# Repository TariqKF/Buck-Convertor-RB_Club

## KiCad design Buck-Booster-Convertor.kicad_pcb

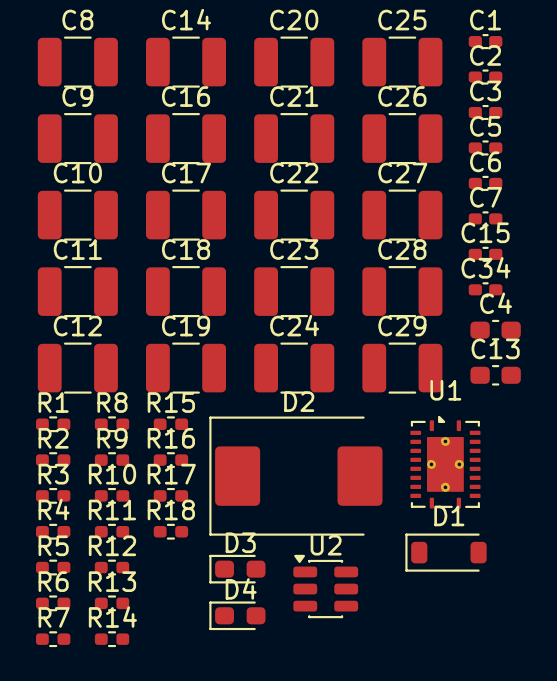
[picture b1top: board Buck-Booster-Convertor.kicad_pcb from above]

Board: 2 copper layers, 54 parts (0 on the bottom side), 24 nets, no tracks yet.

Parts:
C1: 47nF; C_0402_1005Metric_Pad0.74x0.62mm_HandSolder
C2: 220pF; C_0402_1005Metric_Pad0.74x0.62mm_HandSolder
C3: 6.8nF; C_0402_1005Metric_Pad0.74x0.62mm_HandSolder
C4: 2.2uF; C_0603_1608Metric_Pad1.08x0.95mm_HandSolder
C5, C34: 0.1uF; C_0402_1005Metric_Pad0.74x0.62mm_HandSolder
C6: 100pF; C_0402_1005Metric_Pad0.74x0.62mm_HandSolder
C7: 820pF; C_0402_1005Metric_Pad0.74x0.62mm_HandSolder
C8, C9, C10, C11, C12, C14, C16, C17, C18, C19: 10uF; C_1210_3225Metric_Pad1.33x2.70mm_HandSolder
C13: 0.22uF; C_0603_1608Metric_Pad1.08x0.95mm_HandSolder
C15: 33pF; C_0402_1005Metric_Pad0.74x0.62mm_HandSolder
C20, C21, C22, C23, C24, C25, C26, C27, C28, C29: 22uF; C_1210_3225Metric_Pad1.33x2.70mm_HandSolder
D1: D_Schottky; D_SOD-123
D2: SMDJ20CA; D_SMC
D3: GREEN; LED_0603_1608Metric_Pad1.05x0.95mm_HandSolder
D4: RED; LED_0603_1608Metric_Pad1.05x0.95mm_HandSolder
R1: 49.9k; R_0402_1005Metric_Pad0.72x0.64mm_HandSolder
R2, R4: 7.5k; R_0402_1005Metric_Pad0.72x0.64mm_HandSolder
R3: 80.6k; R_0402_1005Metric_Pad0.72x0.64mm_HandSolder
R5: 100k; R_0402_1005Metric_Pad0.72x0.64mm_HandSolder
R6: 4.7; R_0402_1005Metric_Pad0.72x0.64mm_HandSolder
R7, R8, R10, R11: 1.5; R_0402_1005Metric_Pad0.72x0.64mm_HandSolder
R9: 33.2k; R_0402_1005Metric_Pad0.72x0.64mm_HandSolder
R12: 196; R_0402_1005Metric_Pad0.72x0.64mm_HandSolder
R13: 2.87k; R_0402_1005Metric_Pad0.72x0.64mm_HandSolder
R14: 2.37k; R_0402_1005Metric_Pad0.72x0.64mm_HandSolder
R15, R16: 2.2; R_0402_1005Metric_Pad0.72x0.64mm_HandSolder
R17, R18: 3.3K; R_0402_1005Metric_Pad0.72x0.64mm_HandSolder
U1: LM5145RGYR; Texas_RGY_R-PVQFN-N20_EP2.05x3.05mm_ThermalVias
U2: LM74700; SOT-23-6

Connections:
4S: C8.1, C9.1, C10.1, C11.1, C12.1, C14.1, C16.1, C17.1, C18.1, C19.1, R3.2, R6.1, U2.4 (CATHODE)
12V: C20.1, C21.1, C22.1, C23.1, C24.1, C25.1, C26.1, C27.1, C28.1, C29.1, D1.2 (A), R9.1, R13.2, R17.2
FB: C2.2, C3.2, C7.1, R9.2, R14.1, U1.5 (FB)
GNDREF: C1.1, C4.2, C5.2, C6.2, C8.2, C9.2, C10.2, C11.2, C12.2, C14.2, C15.2, C16.2, C17.2, C18.2, C19.2, C20.2, C21.2, C22.2, C23.2, C24.2, C25.2, C26.2, C27.2, C28.2, C29.2, D2.1 (A1), D3.1 (K), R1.2, R2.1, R14.2, U1.6 (AGND), U1.12 (PGND), U1.15 (EP), U1.21 (EP), U2.2 (GND)
HO: R7.1, R8.1, U1.18 (HO)
LO: R10.1, R11.1, U1.13 (LO)
unnamed: C3.1, R4.2
unnamed: C6.1, R15.2
unnamed: C7.2, R13.1
unnamed: C13.1, R16.2
unnamed: C4.1, D1.1 (K), R5.1, U1.8 (SYNCIN), U1.14 (VCC)
unnamed: D3.2 (A), R17.1
unnamed: D4.2 (A), R18.1
unnamed: R16.1, U1.17 (BST)
unnamed: C2.1, R4.1, U1.4 (COMP)
unnamed: R2.2, R3.1, U1.1 (EN_UVLO)
unnamed: C15.1, R12.1, U1.11 (ILIM)
unnamed: R5.2, U1.10 (PGOOD)
unnamed: R1.1, U1.2 (RT)
unnamed: C1.2, U1.3 (SS_TRK)
unnamed: C5.1, R6.2, U1.20 (VIN)
unnamed: C34.1, U2.1 (VCAP)
SW: C13.2, R12.2, R15.1, U1.19 (SW)
VBAT_F: C34.2, D2.2 (A2), D4.1 (K), U2.3 (EN), U2.6 (ANODE)
